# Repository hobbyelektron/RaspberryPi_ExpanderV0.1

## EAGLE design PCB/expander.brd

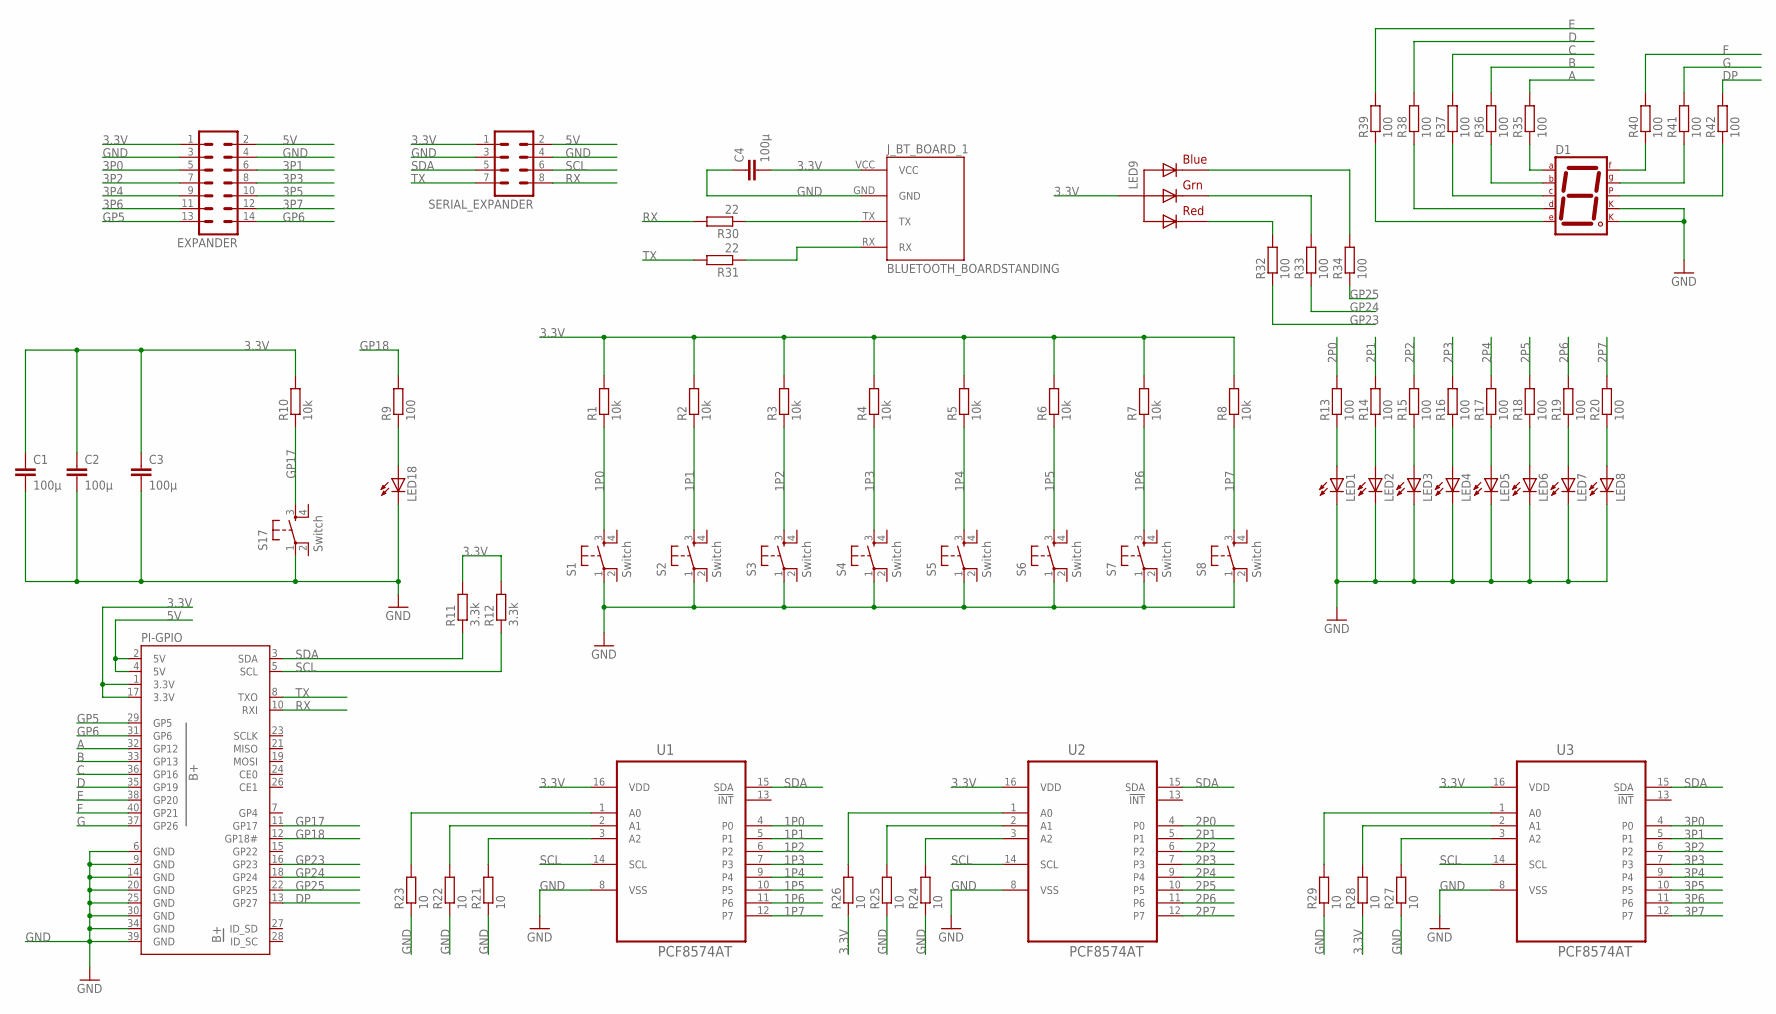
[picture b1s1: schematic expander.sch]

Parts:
C1, C2, C3, C4: 100µ; C0805
D1: 7SEG-CK; 7SEG-13
EXPANDER: MA07-2
J_BT_BOARD_1: BLUETOOTH_BOARDSTANDING; BT_BOARD_FOOTPRINT_STANDING
LED1, LED2, LED3, LED4, LED5, LED6, LED7, LED8, LED18: LEDCHIP-LED0805; CHIP-LED0805
LED9: RGBLED_CA-5MM; LED5MMRGB
PI-GPIO: RASPBERRYPI-B+-GPIO; 2X20-SHROUDED
R1, R2, R3, R4, R5, R6, R7, R8, R10: 10k; R0805
R9, R13, R14, R15, R16, R17, R18, R19, R20, R32, R33, R34, R35, R36, R37, R38, R39, R40, R41, R42: 100; R0805
R11, R12: 3.3k; R0805
R21, R22, R23, R24, R25, R26, R27, R28, R29: 10; R0805
R30, R31: 22; R0805
S1, S2, S3, S4, S5, S6, S7, S8, S17: Switch; TAC-SWITCH-PTH
SERIAL_EXPANDER: MA04-2
U1, U2, U3: PCF8574AT; SOIC127P1032X265-16N

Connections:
1P0: R1.1, S1.3, U1.4 (P0)
1P1: R2.1, S2.3, U1.5 (P1)
1P2: R3.1, S3.3, U1.6 (P2)
1P3: R4.1, S4.3, U1.7 (P3)
1P4: R5.1, S5.3, U1.9 (P4)
1P5: R6.1, S6.3, U1.10 (P5)
1P6: R7.1, S7.3, U1.11 (P6)
1P7: R8.1, S8.3, U1.12 (P7)
2P0: R13.2, U2.4 (P0)
2P1: R14.2, U2.5 (P1)
2P2: R15.2, U2.6 (P2)
2P3: R16.2, U2.7 (P3)
2P4: R17.2, U2.9 (P4)
2P5: R18.2, U2.10 (P5)
2P6: R19.2, U2.11 (P6)
2P7: R20.2, U2.12 (P7)
3.3V: C1.1, C2.1, C3.1, C4.2, EXPANDER.1, J_BT_BOARD_1.VCC, LED9.2 (VCC), PI-GPIO.1 (3.3V), PI-GPIO.17 (3.3V), R1.2, R2.2, R3.2, R4.2, R5.2, R6.2, R7.2, R8.2, R10.2, R11.2, R12.2, R26.1, R28.1, SERIAL_EXPANDER.1, U1.16 (VDD), U2.16 (VDD), U3.16 (VDD)
3P0: EXPANDER.5, U3.4 (P0)
3P1: EXPANDER.6, U3.5 (P1)
3P2: EXPANDER.7, U3.6 (P2)
3P3: EXPANDER.8, U3.7 (P3)
3P4: EXPANDER.9, U3.9 (P4)
3P5: EXPANDER.10, U3.10 (P5)
3P6: EXPANDER.11, U3.11 (P6)
3P7: EXPANDER.12, U3.12 (P7)
5V: EXPANDER.2, PI-GPIO.2 (5V), PI-GPIO.4 (5V), SERIAL_EXPANDER.2
A: PI-GPIO.32 (GP12), R35.2
B: PI-GPIO.33 (GP13), R36.2
C: PI-GPIO.36 (GP16), R37.2
D: PI-GPIO.35 (GP19), R38.2
DP: PI-GPIO.13 (GP27), R42.2
E: PI-GPIO.38 (GP20), R39.2
F: PI-GPIO.40 (GP21), R40.2
G: PI-GPIO.37 (GP26), R41.2
GND: C1.2, C2.2, C3.2, C4.1, D1.3 (CK1), D1.8 (CK2), EXPANDER.3, EXPANDER.4, J_BT_BOARD_1.GND, LED1.C, LED2.C, LED3.C, LED4.C, LED5.C, LED6.C, LED7.C, LED8.C, LED18.C, PI-GPIO.6 (GND), PI-GPIO.9 (GND), PI-GPIO.14 (GND), PI-GPIO.20 (GND), PI-GPIO.25 (GND), PI-GPIO.30 (GND), PI-GPIO.34 (GND), PI-GPIO.39 (GND), R21.1, R22.1, R23.1, R24.1, R25.1, R27.1, R29.1, S1.1, S2.1, S3.1, S4.1, S5.1, S6.1, S7.1, S8.1, S17.1, SERIAL_EXPANDER.3, SERIAL_EXPANDER.4, U1.8 (VSS), U2.8 (VSS), U3.8 (VSS)
GP5: EXPANDER.13, PI-GPIO.29 (GP5)
GP6: EXPANDER.14, PI-GPIO.31 (GP6)
GP17: PI-GPIO.11 (GP17), R10.1, S17.3
GP18: PI-GPIO.12 (GP18#), R9.2
GP23: PI-GPIO.16 (GP23), R32.1
GP24: PI-GPIO.18 (GP24), R33.1
GP25: PI-GPIO.22 (GP25), R34.1
unnamed: LED18.A, R9.1
unnamed: LED1.A, R13.1
unnamed: LED2.A, R14.1
unnamed: LED3.A, R15.1
unnamed: LED4.A, R16.1
unnamed: LED5.A, R17.1
unnamed: LED6.A, R18.1
unnamed: LED7.A, R19.1
unnamed: LED8.A, R20.1
unnamed: R21.2, U1.3 (A2)
unnamed: R22.2, U1.2 (A1)
unnamed: R23.2, U1.1 (A0)
unnamed: R24.2, U2.3 (A2)
unnamed: R25.2, U2.2 (A1)
unnamed: R26.2, U2.1 (A0)
unnamed: R27.2, U3.3 (A2)
unnamed: R28.2, U3.2 (A1)
unnamed: R29.2, U3.1 (A0)
unnamed: LED9.4 (BLUE), R34.2
unnamed: LED9.3 (GREEN), R33.2
unnamed: J_BT_BOARD_1.TX, R30.1
unnamed: J_BT_BOARD_1.RX, R31.1
unnamed: LED9.1 (RED), R32.2
unnamed: D1.7 (A), R35.1
unnamed: D1.6 (B), R36.1
unnamed: D1.4 (C), R37.1
unnamed: D1.2 (D), R38.1
unnamed: D1.1 (E), R39.1
unnamed: D1.9 (F), R40.1
unnamed: D1.10 (G), R41.1
unnamed: D1.5 (DP), R42.1
RX: PI-GPIO.10 (RXI), R30.2, SERIAL_EXPANDER.8
SCL: PI-GPIO.5 (SCL), R12.1, SERIAL_EXPANDER.6, U1.14 (SCL), U2.14 (SCL), U3.14 (SCL)
SDA: PI-GPIO.3 (SDA), R11.1, SERIAL_EXPANDER.5, U1.15 (SDA), U2.15 (SDA), U3.15 (SDA)
TX: PI-GPIO.8 (TXO), R31.2, SERIAL_EXPANDER.7

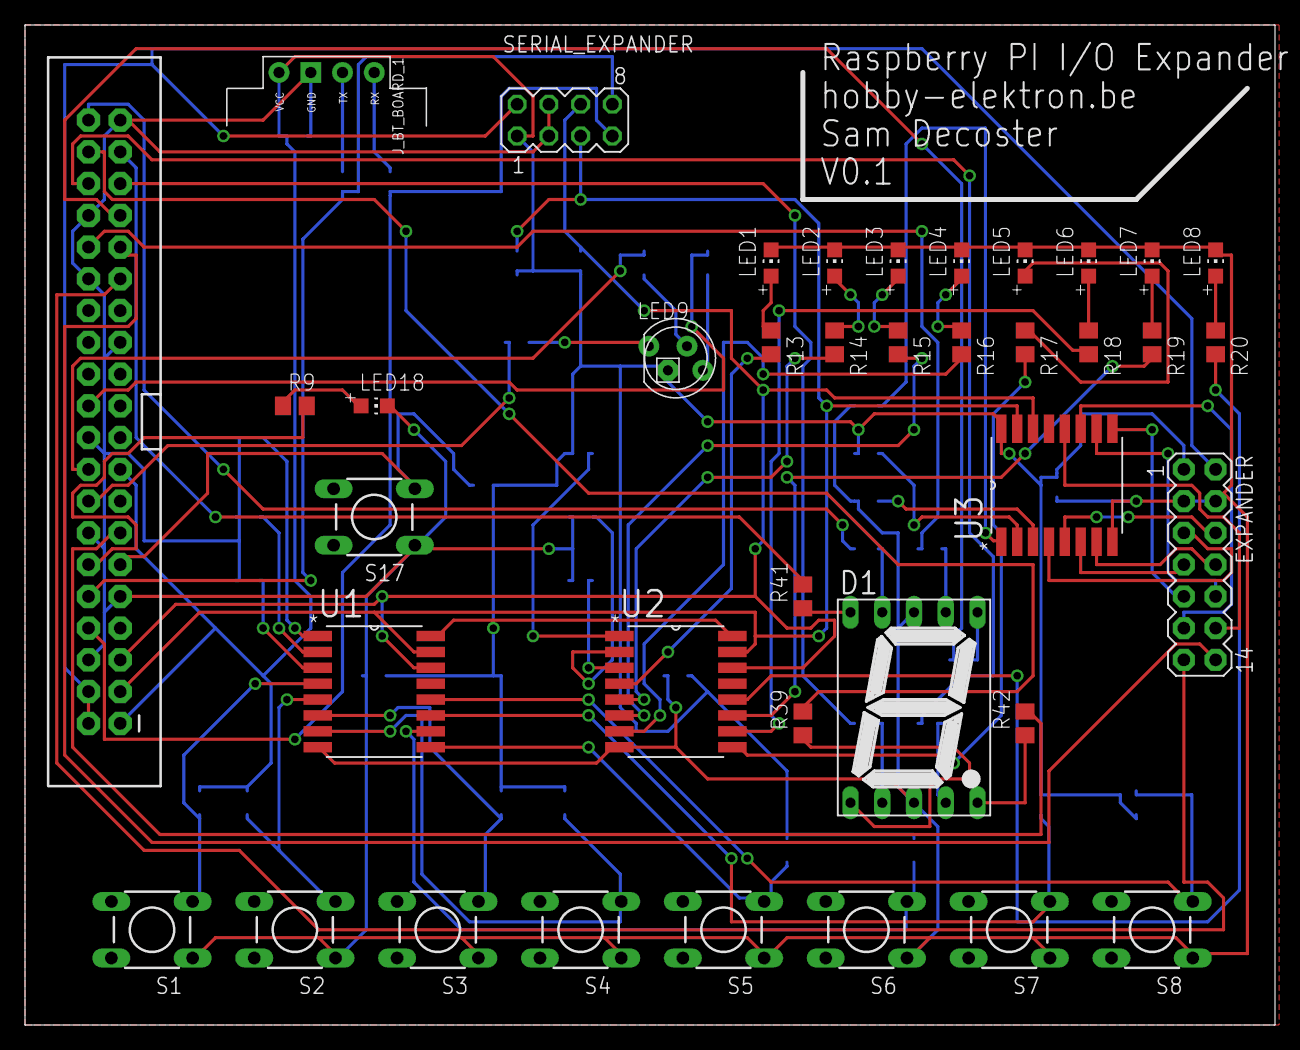
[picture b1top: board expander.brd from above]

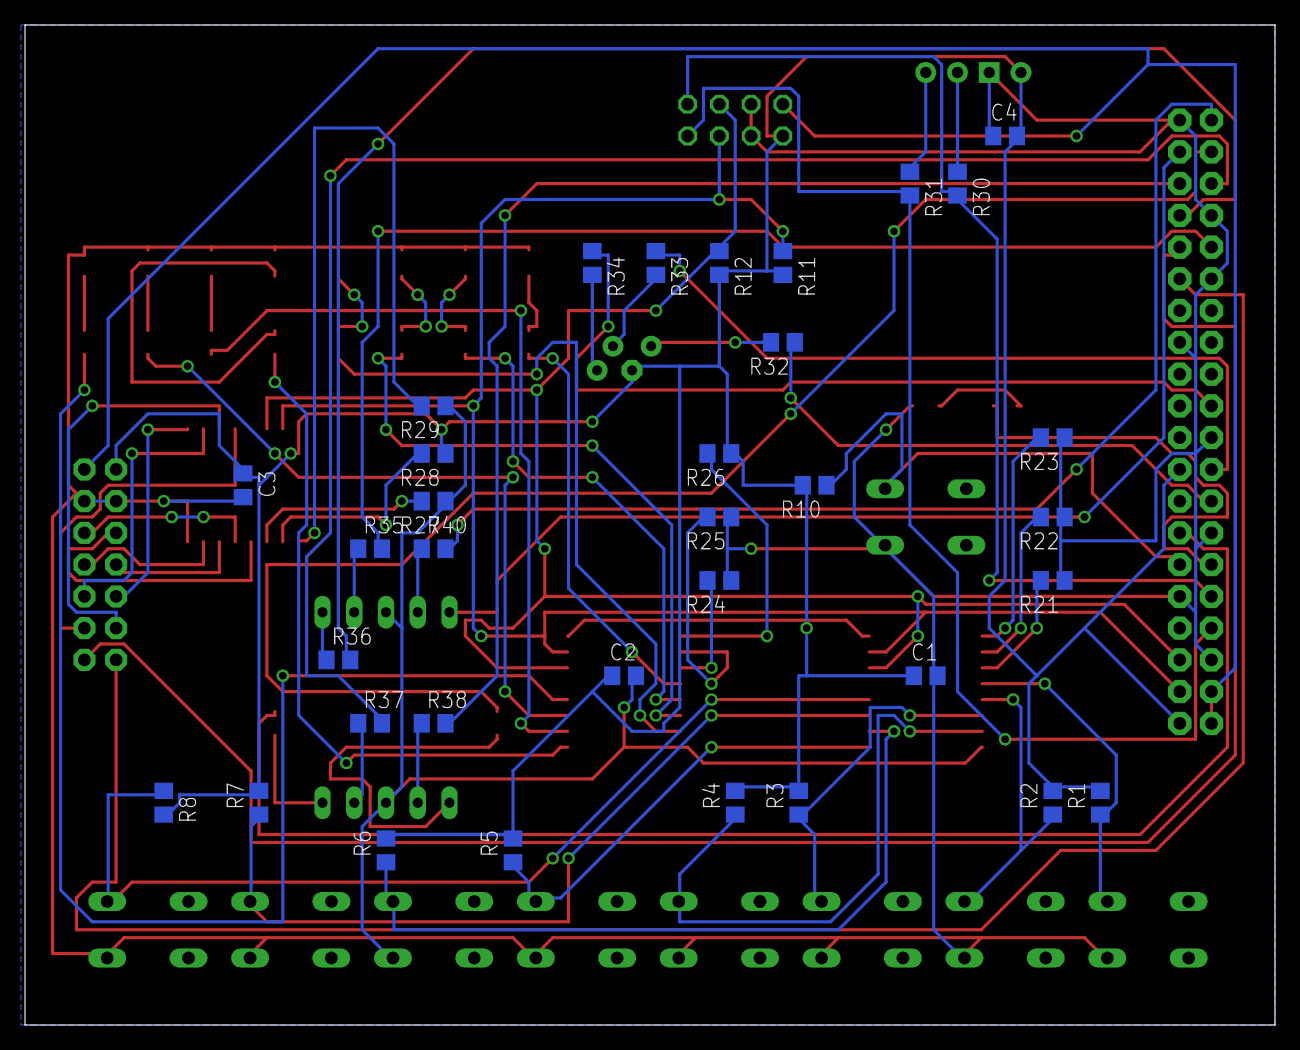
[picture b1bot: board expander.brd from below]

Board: 2 copper layers, 100.0 x 80.0 mm, 73 parts (34 on the bottom side), 77 nets.

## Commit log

2015-04-28 add PCB files
2015-04-28 add documentation file
2015-04-28 add software: LED_Blink.py
2015-04-28 add button read software for python
2015-04-28 add button to led script
2015-04-28 add .docx component list
2015-04-28 add packages
2015-04-28 move file
2015-04-28 add module
2015-04-30 new software
2015-04-30 add site
2015-05-02 add software

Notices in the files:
parts and their libraries:
SparkFun-Boards: Licensing: Creative Commons ShareAlike 4.0 International - https://creativecommons.org/licenses/by-sa/4.0
